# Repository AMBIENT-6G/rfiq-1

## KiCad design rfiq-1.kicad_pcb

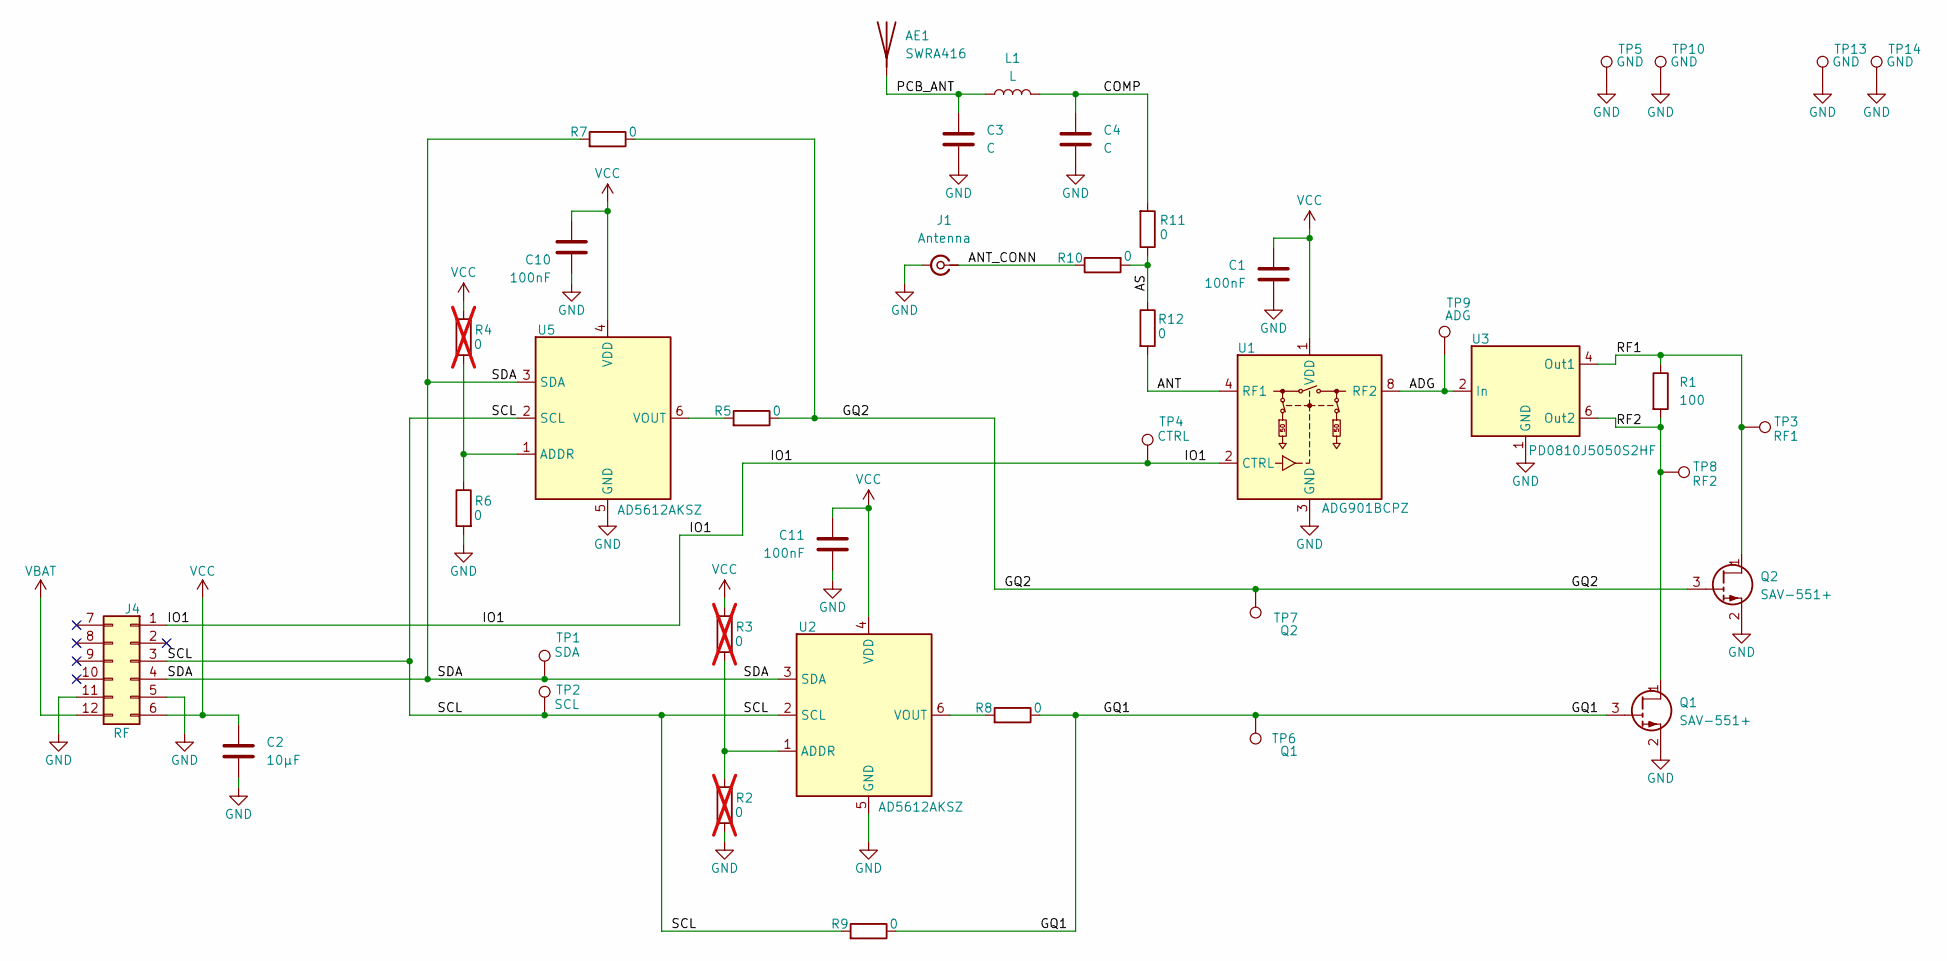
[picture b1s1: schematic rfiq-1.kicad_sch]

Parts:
AE1: SWRA416; Texas_SWRA416_868MHz_915MHz
C1, C10, C11: 100nF; C_0603_1608Metric; Part Number MAJCU168BB7104KTEA01
C2: 10µF; C_0603_1608Metric; Part Number GXT188R61C106KE13D
C3, C4: C; C_0402_1005Metric
J1: Antenna; SMA_Amphenol_901-144_Vertical; Part Number RFPC-SMA28-F
J4: RF; PMOD_2x06_P2.54mm_Male; Part Number 61301221021
L1: L; L_0402_1005Metric
Q1, Q2: SAV-551+; SC-82AA; Part Number SAV-551+
R1: 100; R_0603_1608Metric; Part Number TR0603MR-07100RL
R2, R3, R4: 0; R_0603_1608Metric; Part Number CRCW06030000Z0EI; not fitted
R5, R6, R7, R8, R9: 0; R_0603_1608Metric; Part Number CRCW06030000Z0EI
R10, R11, R12: 0; R_0402_1005Metric; Part Number CRCW06030000Z0EI
TP1: SDA; Testpoint_THT
TP2: SCL; Testpoint_THT
TP3: RF1; Testpoint_SMD_S
TP4: CTRL; Testpoint_THT
TP5, TP10, TP13: GND; Testpoint_THT
TP6: Q1; Testpoint_THT
TP7: Q2; Testpoint_THT
TP8: RF2; Testpoint_SMD_S
TP9: ADG; Testpoint_SMD_S
TP14: GND; Testpoint_SMD_S
U1: ADG901BCPZ; LFCSP-8-1EP_3x3mm_P0.5mm_EP1.45x1.74mm; Part Number ADG901BCPZ-500RL7
U2, U5: AD5612AKSZ; SOT-363_SC-70-6; Part Number AD5612AKSZ-2500RL7
U3: PD0810J5050S2HF; Part Number PD0810J5050S2HF

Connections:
/ADG: TP9.1, U1.8 (RF2), U3.2 (In)
/ANT: R12.2, U1.4 (RF1)
/ANT_CONN: J1.1 (In), R10.1
/AS: R10.2, R11.1, R12.1
/COMP: C4.1, L1.2, R11.2
/GQ1: Q1.3 (G), R8.1, R9.1, TP6.1
/GQ2: Q2.3 (G), R5.1, R7.1, TP7.1
/IO1: J4.1, TP4.1, U1.2 (CTRL)
/PCB_ANT: AE1.1 (A), C3.1, L1.1
/RF1: Q2.1 (D), R1.1, TP3.1, U3.4 (Out1)
/RF2: Q1.1 (D), R1.2, TP8.1, U3.6 (Out2)
/SCL: J4.3, R9.2, TP2.1, U2.2 (SCL), U5.2 (SCL)
/SDA: J4.4, R7.2, TP1.1, U2.3 (SDA), U5.3 (SDA)
GND: C1.2, C2.2, C3.2, C4.2, C10.2, C11.2, J1.2 (Ext), J4.5, J4.11, Q1.2 (S), Q1.4 (S), Q2.2 (S), Q2.4 (S), R2.2, R6.2, TP5.1, TP10.1, TP13.1, TP14.1, U1.3 (GND), U1.5 (GND), U1.6 (GND), U1.7 (GND), U1.9 (GND), U2.5 (GND), U3.1 (GND), U3.3 (GND), U3.5 (GND), U5.5 (GND)
unnamed: R2.1, R3.2, U2.1 (ADDR)
unnamed: R8.2, U2.6 (VOUT)
unnamed: R4.2, R6.1, U5.1 (ADDR)
unnamed: R5.2, U5.6 (VOUT)
VBAT: J4.12
VCC: C1.1, C2.1, C10.1, C11.1, J4.6, R3.1, R4.1, U1.1 (VDD), U2.4 (VDD), U5.4 (VDD)

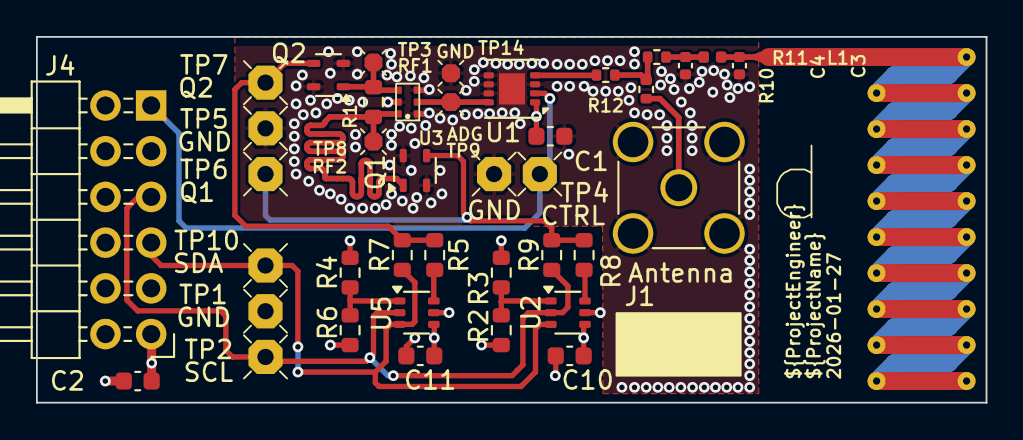
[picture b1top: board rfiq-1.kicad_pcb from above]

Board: 4 copper layers, 52.8 x 20.3 mm, 40 parts (0 on the bottom side), 19 nets.

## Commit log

2026-02-02 First version put into production.
2026-02-02 Adding gitignore.
